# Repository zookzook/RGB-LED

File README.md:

# RGB-LED
Simple board, that turns analog RGB input into colourful light.

# How does it work?
Three analog inputs for red, green and blue determine the values of the color. The values are 
transferred to the WS2811, which is used to drive the RGB LED.

The switch allows the flashing of the RGB LED to be switched on and off.

# Board preview

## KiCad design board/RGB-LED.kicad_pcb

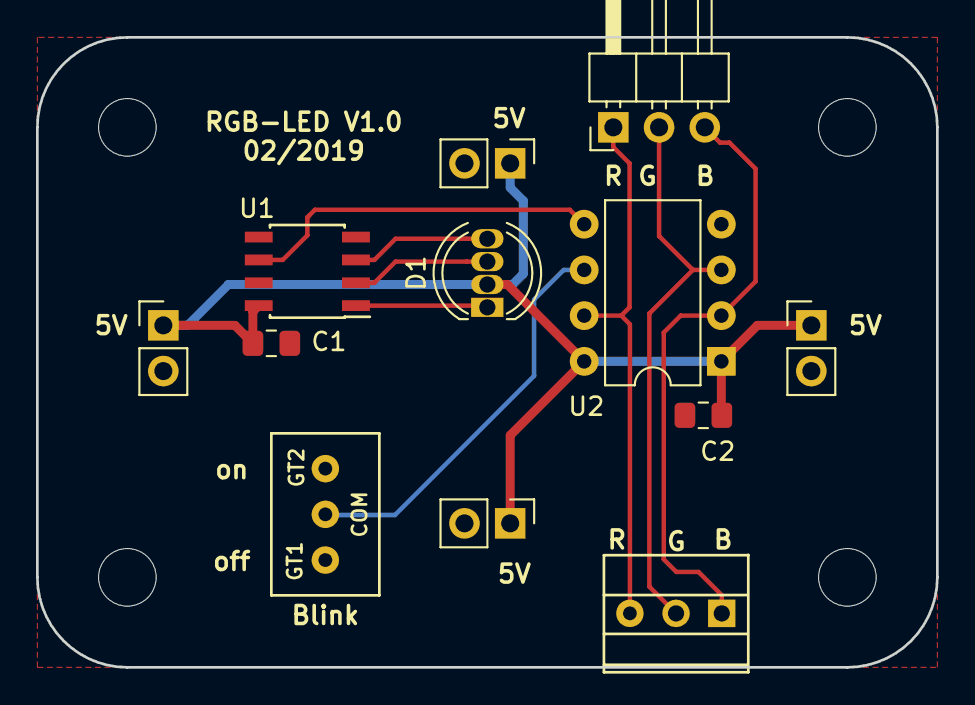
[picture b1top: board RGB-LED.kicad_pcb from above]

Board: 2 copper layers, 50.0 x 35.0 mm, 12 parts (0 on the bottom side), 10 nets.

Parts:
C1: 100nF; C_0805_2012Metric_Pad1.15x1.40mm_HandSolder
C2: C_Small; C_0805_2012Metric_Pad1.15x1.40mm_HandSolder
D1: LED_RAGB; LED_D5.0mm-4_RGB
J1, J2, J5, J6: SUPPLY; PinHeader_1x02_P2.54mm_Vertical
J3: Screw_Terminal_01x03; AKZ692_3_2_54
J4: Conn_01x03_Female; PinHeader_1x03_P2.54mm_Horizontal
SW1: SW_Push_SPDT; MS-611A
U1: WS2811; SOIC-8_3.9x4.9mm_P1.27mm
U2: ATtiny85-20PU; DIP-8_W7.62mm

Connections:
+5V: C1.1, C2.1, D1.2, J1.1, J2.1, J5.1, J6.1, U1.8, U2.1, U2.8
/ANALOG_BLUE: J3.1, J4.3, U2.2
/ANALOG_GREEN: J3.2, J4.2, U2.3
/ANALOG_RED: J3.3, J4.1, U2.7
/DO: U1.6, U2.5
GND: C1.2, C2.2, J1.2, J2.2, J5.2, J6.2, SW1.1, U1.4, U2.4
unnamed: D1.1, U1.1
unnamed: D1.3, U1.2
unnamed: D1.4, U1.3
unnamed: SW1.2, U2.6

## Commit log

2019-02-10 fixed typo
2019-02-10 added 3d models
2019-02-10 added doc
